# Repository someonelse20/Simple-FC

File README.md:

# Simple-FC

A RP2350 based flight controller with a 10-axis IMU. This board is designed to be used for drones and had four PWM outputs to control ESCs as well as UART and I2C to communicate with other boards.

## Overview
- **MCU**: RP2350
- **Gyroscope/Accelerometer**: LSM6DSM
- **Magnetometer**: MMC5983MA
- **Barometer**: BMP384
- **External Storage**: Micro SD card
- **MCU Storage**: 16MB
- **Input Voltage**: 1.2V-5.3V
- **I/O**: 
    - 4 PWM
    - 2 UART
    - 2 I2C
    - USB C

### Schematic

### PCB

## BOM
The BOM is located in BOM.csv and DigiKeyBOM.csv for ordering the parts from DikiKey. Alternatively the DigiKey BOM can be found [here](https://www.digikey.com/en/mylists/list/84RC15SOU8).

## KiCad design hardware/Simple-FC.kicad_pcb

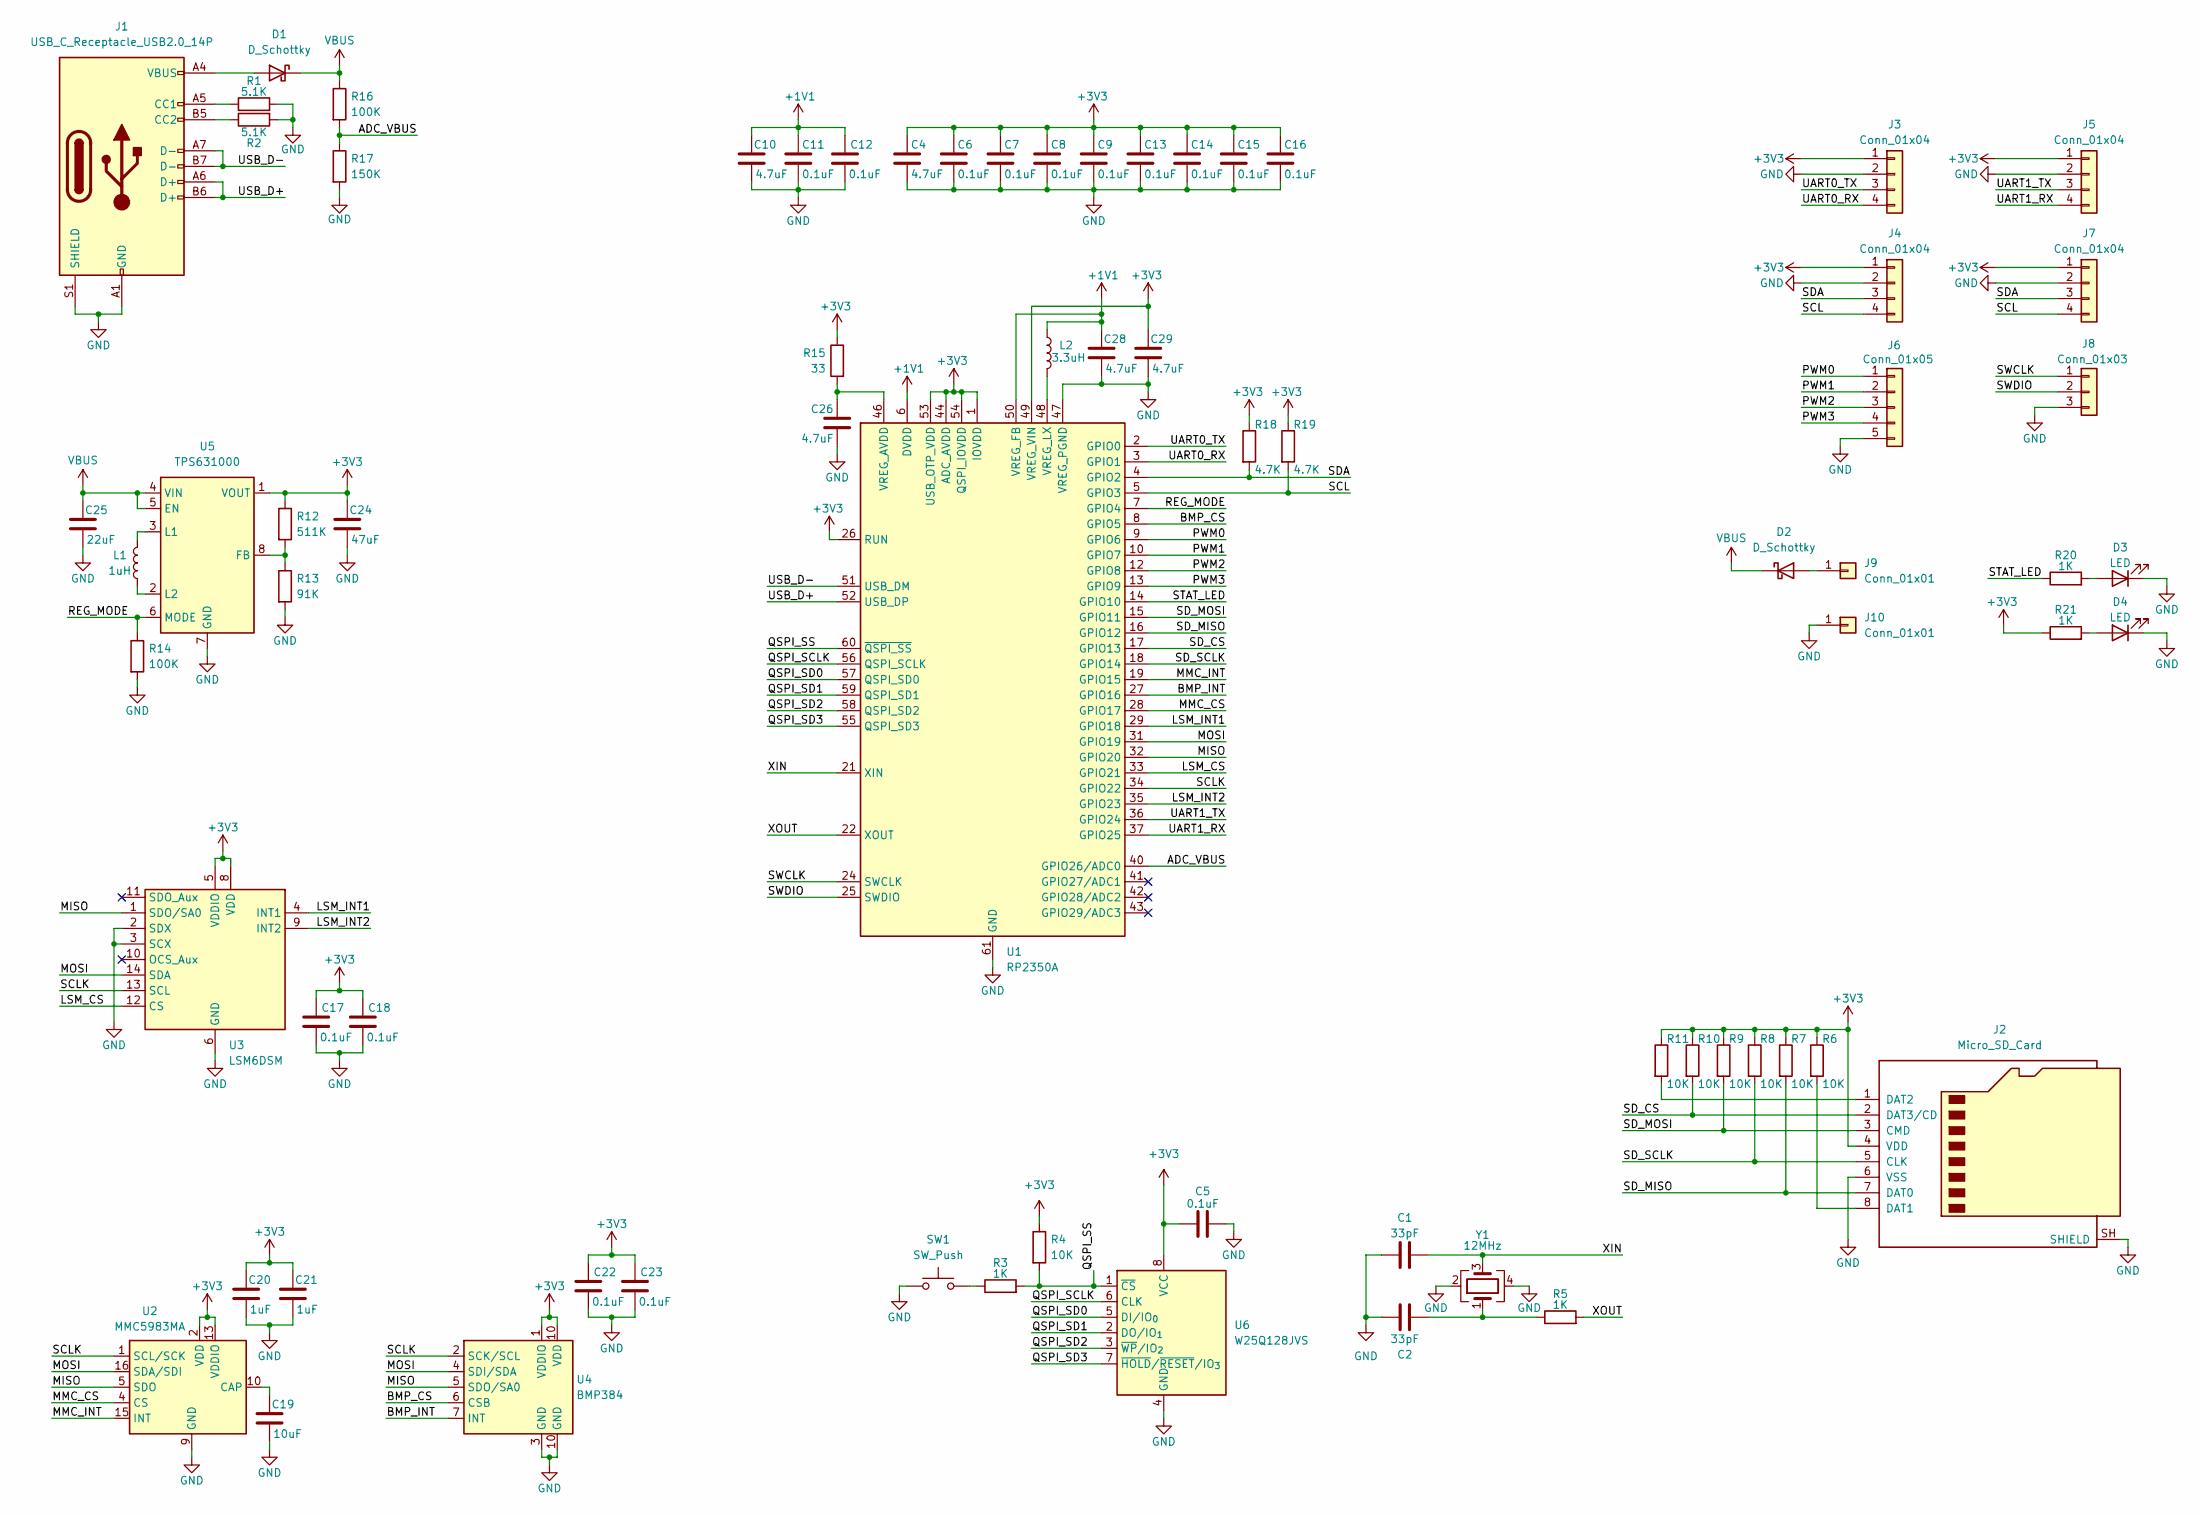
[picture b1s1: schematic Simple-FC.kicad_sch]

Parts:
C1, C2: 33pF; C_0402_1005Metric; MPN CL05C330JB5NNNC
C4, C10, C26, C28, C29: 4.7uF; C_0402_1005Metric; MPN GRM155R60J475ME47D
C5, C6, C7, C8, C9, C11, C12, C13, C14, C15, C16, C17, C18, C22, C23: 0.1uF; C_0402_1005Metric; MPN GRM155R71H104KE14D
C19: 10uF; C_0603_1608Metric; MPN GRM188R61A106ME69D
C20, C21: 1uF; C_0402_1005Metric; MPN CL05A105KO5NNNC
C24: 47uF; C_0603_1608Metric; MPN GRM188R60J476ME15D
C25: 22uF; C_0603_1608Metric; MPN C1608X5R0J226M080AC
D1, D2: D_Schottky; D_SMA; MPN SS210A
D3: LED; LED_0603_1608Metric; MPN LTST-C190GKT
D4: LED; LED_0603_1608Metric; MPN LTST-C190KRKT
J1: USB_C_Receptacle_USB2.0_14P; USB_C_Receptacle_HRO_TYPE-C-31-M-12; MPN UJ20-C-H-G-SMT-1-P16-TR
J2: Micro_SD_Card; microSD_HC_Molex_47219-2001; MPN MSD-7-A
J3, J4, J5, J7: Conn_01x04; PinHeader_1x04_P2.54mm_Vertical
J6: Conn_01x05; PinHeader_1x05_P2.54mm_Vertical
J8: Conn_01x03; PinHeader_1x03_P2.54mm_Vertical
J9, J10: Conn_01x01; SolderWirePad_1x01_SMD_1x2mm
L1: 1uH; L_0805_2012Metric; MPN DFE201210U-1R0M=P2
L2: 3.3uH; L_0805_2012Metric; MPN AOTA-B201610S3R3-101-T
R1, R2: 5.1K; R_0402_1005Metric; MPN RC0402FR-075K1L
R3, R5, R20, R21: 1K; R_0402_1005Metric; MPN ERJ-2RKF1001X
R4, R6, R7, R8, R9, R10, R11: 10K; R_0402_1005Metric; MPN RC0402FR-0710KL
R12: 511K; R_0402_1005Metric; MPN RC0402FR-13511KL
R13: 91K; R_0402_1005Metric; MPN RK73H1ETTP9102F
R14, R16: 100K; R_0402_1005Metric; MPN RC0402FR-07100KL
R15: 33; R_0402_1005Metric; MPN RC0402FR-0733RL
R17: 150K; R_0402_1005Metric; MPN CPF0402B150KE1
R18, R19: 4.7K; R_0402_1005Metric; MPN RK73H1ETTP4701F
SW1: SW_Push; SW_Push_SPST_NO_Alps_SKRK; MPN SKRKAEE020
U1: RP2350A; QFN-60-1EP_7x7mm_P0.4mm_EP3.4x3.4mm; MPN RP2350A
U2: MMC5983MA; LGA-16_3x3mm_P0.5mm; MPN MMC5983MA
U3: LSM6DSM; LGA-14_3x2.5mm_P0.5mm_LayoutBorder3x4y; MPN LSM6DSMTR
U4: BMP384; ST_HLGA-10_2x2mm_P0.5mm_LayoutBorder3x2y; MPN BMP384
U5: TPS631000; SOT-583-8; MPN TPS631000DRLR
U6: W25Q128JVS; Winbond_USON-8-1EP_3x2mm_P0.5mm_EP0.2x1.6mm; MPN W25Q128JVSIQ TR
Y1: 12MHz; Crystal_SMD_3225-4Pin_3.2x2.5mm; MPN ABM8-272-T3

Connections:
+1V1: C10.1, C11.1, C12.1, C28.1, L2.1, U1.6 (DVDD), U1.23 (DVDD), U1.39 (DVDD), U1.50 (VREG_FB)
/ADC_VBUS: R16.2, R17.1, U1.40 (GPIO26/ADC0)
/BMP_CS: U1.8 (GPIO5), U4.6 (CSB)
/BMP_INT: U1.27 (GPIO16), U4.7 (INT)
/LSM_CS: U1.33 (GPIO21), U3.12 (CS)
/LSM_INT1: U1.29 (GPIO18), U3.4 (INT1)
/LSM_INT2: U1.35 (GPIO23), U3.9 (INT2)
/MISO: U1.32 (GPIO20), U2.5 (SDO), U3.1 (SDO/SA0), U4.5 (SDO/SA0)
/MMC_CS: U1.28 (GPIO17), U2.4 (CS)
/MMC_INT: U1.19 (GPIO15), U2.15 (INT)
/MOSI: U1.31 (GPIO19), U2.16 (SDA/SDI), U3.14 (SDA), U4.4 (SDI/SDA)
/PWM0: J6.1, U1.9 (GPIO6)
/PWM1: J6.2, U1.10 (GPIO7)
/PWM2: J6.3, U1.12 (GPIO8)
/PWM3: J6.4, U1.13 (GPIO9)
/QSPI_SCLK: U1.56 (QSPI_SCLK), U6.6 (CLK)
/QSPI_SD0: U1.57 (QSPI_SD0), U6.5 (DI/IO_{0})
/QSPI_SD1: U1.59 (QSPI_SD1), U6.2 (DO/IO_{1})
/QSPI_SD2: U1.58 (QSPI_SD2), U6.3 (~WP/IO_{2})
/QSPI_SD3: U1.55 (QSPI_SD3), U6.7 (~HOLD/~RESET/IO_{3})
/QSPI_SS: R3.2, R4.2, U1.60 (~QSPI_SS), U6.1 (~CS)
/REG_MODE: R14.1, U1.7 (GPIO4), U5.6 (MODE)
/SCL: J4.4, J7.4, R19.2, U1.5 (GPIO3)
/SCLK: U1.34 (GPIO22), U2.1 (SCL/SCK), U3.13 (SCL), U4.2 (SCK/SCL)
/SDA: J4.3, J7.3, R18.2, U1.4 (GPIO2)
/SD_CS: J2.2 (DAT3/CD), R10.2, U1.17 (GPIO13)
/SD_MISO: J2.7 (DAT0), R7.2, U1.16 (GPIO12)
/SD_MOSI: J2.3 (CMD), R9.2, U1.15 (GPIO11)
/SD_SCLK: J2.5 (CLK), R8.2, U1.18 (GPIO14)
/STAT_LED: R20.1, U1.14 (GPIO10)
/SWCLK: J8.1, U1.24 (SWCLK)
/SWDIO: J8.2, U1.25 (SWDIO)
/UART0_RX: J3.4, U1.3 (GPIO1)
/UART0_TX: J3.3, U1.2 (GPIO0)
/UART1_RX: J5.4, U1.37 (GPIO25)
/UART1_TX: J5.3, U1.36 (GPIO24)
/USB_D+: J1.A6 (D+), J1.B6 (D+), U1.52 (USB_DP)
/USB_D-: J1.A7 (D-), J1.B7 (D-), U1.51 (USB_DM)
/XIN: C1.2, U1.21 (XIN), Y1.3
/XOUT: R5.2, U1.22 (XOUT)
unnamed: C2.1, R5.1, Y1.1
unnamed: D1.2 (A), J1.A4 (VBUS), J1.A9 (VBUS), J1.B4 (VBUS), J1.B9 (VBUS)
unnamed: D2.2 (A), J9.1 (Pin_1_1)
unnamed: D3.2 (A), R20.2
unnamed: D4.2 (A), R21.2
unnamed: J1.A5 (CC1), R1.1
unnamed: J1.B5 (CC2), R2.1
unnamed: J2.8 (DAT1), R6.2
unnamed: J2.1 (DAT2), R11.2
unnamed: R3.1, SW1.2
unnamed: C26.1, R15.2, U1.46 (VREG_AVDD)
unnamed: L2.2, U1.48 (VREG_LX)
unnamed: C19.1, U2.10 (CAP)
unnamed: R12.2, R13.1, U5.8 (FB)
unnamed: L1.1, U5.3 (L1)
unnamed: L1.2, U5.2 (L2)
VBUS: C25.1, D1.1 (K), D2.1 (K), R16.1, U5.4 (VIN), U5.5 (EN)

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
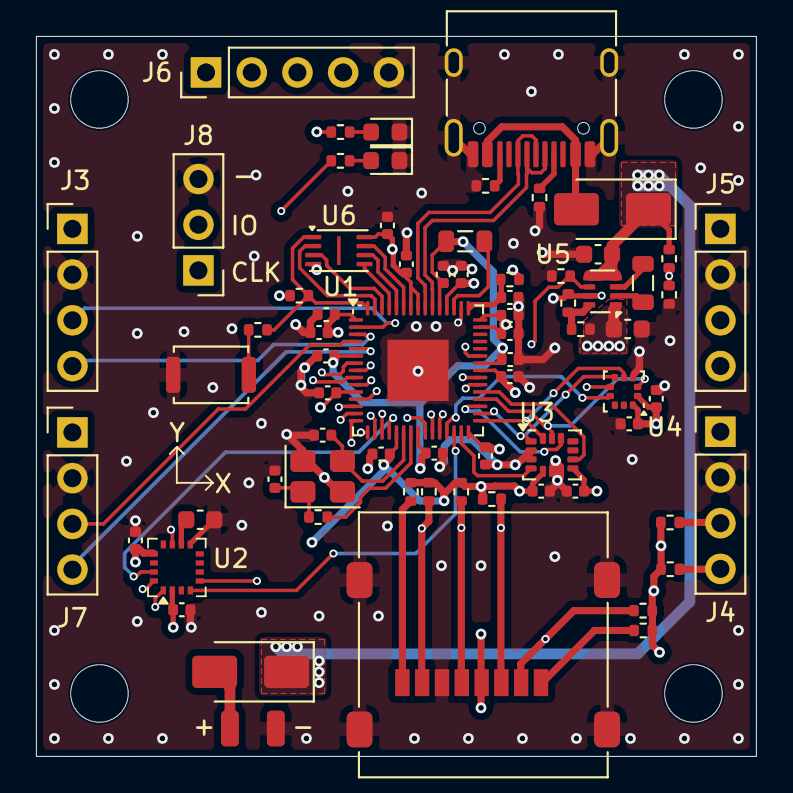
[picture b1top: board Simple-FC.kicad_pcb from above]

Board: 4 copper layers, 40.0 x 40.0 mm, 72 parts (0 on the bottom side), 59 nets.

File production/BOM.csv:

"Reference","Qty","Value","DNP","Exclude from BOM","Exclude from Board","Exclude from Simulation","Exclude from Position Files","Footprint","Datasheet","MPN"
"SW1","1","SW_Push","","","","","${EXCLUDE_FROM_POS_FILES}","Button_Switch_SMD:SW_Push_SPST_NO_Alps_SKRK","","SKRKAEE020"
"C1,C2","2","33pF","","","","","${EXCLUDE_FROM_POS_FILES}","Capacitor_SMD:C_0402_1005Metric","","CL05C330JB5NNNC"
"C4,C10,C26,C28,C29","5","4.7uF","","","","","${EXCLUDE_FROM_POS_FILES}","Capacitor_SMD:C_0402_1005Metric","","GRM155R60J475ME47D"
"C5,C6,C7,C8,C9,C11,C12,C13,C14,C15,C16,C17,C18,C22,C23","15","0.1uF","","","","","${EXCLUDE_FROM_POS_FILES}","Capacitor_SMD:C_0402_1005Metric","","GRM155R71H104KE14D"
"C20,C21","2","1uF","","","","","${EXCLUDE_FROM_POS_FILES}","Capacitor_SMD:C_0402_1005Metric","","CL05A105KO5NNNC"
"C19","1","10uF","","","","","${EXCLUDE_FROM_POS_FILES}","Capacitor_SMD:C_0603_1608Metric","","GRM188R61A106ME69D"
"C24","1","47uF","","","","","${EXCLUDE_FROM_POS_FILES}","Capacitor_SMD:C_0603_1608Metric","","GRM188R60J476ME15D"
"C25","1","22uF","","","","","${EXCLUDE_FROM_POS_FILES}","Capacitor_SMD:C_0603_1608Metric","","C1608X5R0J226M080AC"
"J2","1","Micro_SD_Card","","","","","${EXCLUDE_FROM_POS_FILES}","Connector_Card:microSD_HC_Molex_47219-2001","https://www.we-online.com/components/products/datasheet/6930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","MSD-7-A"
"J8","1","Conn_01x03","DNP","","","","${EXCLUDE_FROM_POS_FILES}","Connector_PinHeader_2.54mm:PinHeader_1x03_P2.54mm_Vertical","",""
"J3,J4,J5,J7","4","Conn_01x04","DNP","","","","${EXCLUDE_FROM_POS_FILES}","Connector_PinHeader_2.54mm:PinHeader_1x04_P2.54mm_Vertical","",""
"J6","1","Conn_01x05","DNP","","","","${EXCLUDE_FROM_POS_FILES}","Connector_PinHeader_2.54mm:PinHeader_1x05_P2.54mm_Vertical","",""
"J1","1","USB_C_Receptacle_USB2.0_14P","","","","","${EXCLUDE_FROM_POS_FILES}","Connector_USB:USB_C_Receptacle_HRO_TYPE-C-31-M-12","https://www.usb.org/sites/default/files/documents/usb_type-c.zip","UJ20-C-H-G-SMT-1-P16-TR"
"J9,J10","2","Conn_01x01","DNP","","","","${EXCLUDE_FROM_POS_FILES}","Connector_Wire:SolderWirePad_1x01_SMD_1x2mm","",""
"Y1","1","12MHz","","","","","${EXCLUDE_FROM_POS_FILES}","Crystal:Crystal_SMD_3225-4Pin_3.2x2.5mm","","ABM8-272-T3"
"D1,D2","2","D_Schottky","","","","","${EXCLUDE_FROM_POS_FILES}","Diode_SMD:D_SMA","","SS210A"
"L1","1","1uH","","","","","${EXCLUDE_FROM_POS_FILES}","Inductor_SMD:L_0805_2012Metric","","DFE201210U-1R0M=P2"
"L2","1","3.3uH","","","","","${EXCLUDE_FROM_POS_FILES}","Inductor_SMD:L_0805_2012Metric","","AOTA-B201610S3R3-101-T"
"D3,D4","2","LED","","","","","${EXCLUDE_FROM_POS_FILES}","LED_SMD:LED_0603_1608Metric","","LTST-C190GKT,LTST-C190KRKT"
"U1","1","RP2350A","","","","","${EXCLUDE_FROM_POS_FILES}","Package_DFN_QFN:QFN-60-1EP_7x7mm_P0.4mm_EP3.4x3.4mm","https://datasheets.raspberrypi.com/rp2350/rp2350-datasheet.pdf","RP2350A"
"U3","1","LSM6DSM","","","","","${EXCLUDE_FROM_POS_FILES}","Package_LGA:LGA-14_3x2.5mm_P0.5mm_LayoutBorder3x4y","https://www.st.com/resource/en/datasheet/lsm6dsm.pdf","LSM6DSMTR"
"U2","1","MMC5983MA","","","","","${EXCLUDE_FROM_POS_FILES}","Package_LGA:LGA-16_3x3mm_P0.5mm","https://www.memsic.com/Public/Uploads/uploadfile/files/20220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","MMC5983MA"
"U4","1","BMP384","","","","","${EXCLUDE_FROM_POS_FILES}","Package_LGA:ST_HLGA-10_2x2mm_P0.5mm_LayoutBorder3x2y","https://www.bosch-sensortec.com/media/boschsensortec/downloa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","BMP384"
"U6","1","W25Q128JVS","","","","","${EXCLUDE_FROM_POS_FILES}","Package_SON:Winbond_USON-8-1EP_3x2mm_P0.5mm_EP0.2x1.6mm","https://www.winbond.com/resource-files/w25q128jv_dtr%20revc%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","W25Q128JVSIQ TR"
"U5","1","TPS631000","","","","","${EXCLUDE_FROM_POS_FILES}","Package_TO_SOT_SMD:SOT-583-8","https://www.ti.com/lit/ds/symlink/tps631000.pdf","TPS631000DRLR"
"R1,R2","2","5.1K","","","","","${EXCLUDE_FROM_POS_FILES}","Resistor_SMD:R_0402_1005Metric","","RC0402FR-075K1L"
"R3,R5,R20,R21","4","1K","","","","","${EXCLUDE_FROM_POS_FILES}","Resistor_SMD:R_0402_1005Metric","","ERJ-2RKF1001X"
"R4,R6,R7,R8,R9,R10,R11","7","10K","","","","","${EXCLUDE_FROM_POS_FILES}","Resistor_SMD:R_0402_1005Metric","","RC0402FR-0710KL"
"R12","1","511K","","","","","${EXCLUDE_FROM_POS_FILES}","Resistor_SMD:R_0402_1005Metric","","RC0402FR-13511KL"
"R13","1","91K","","","","","${EXCLUDE_FROM_POS_FILES}","Resistor_SMD:R_0402_1005Metric","","RK73H1ETTP9102F"
"R14,R16","2","100K","","","","","${EXCLUDE_FROM_POS_FILES}","Resistor_SMD:R_0402_1005Metric","","RC0402FR-07100KL"
"R15","1","33","","","","","${EXCLUDE_FROM_POS_FILES}","Resistor_SMD:R_0402_1005Metric","","RC0402FR-0733RL"
"R17","1","150K","","","","","${EXCLUDE_FROM_POS_FILES}","Resistor_SMD:R_0402_1005Metric","","CPF0402B150KE1"
"R18,R19","2","4.7K","","","","","${EXCLUDE_FROM_POS_FILES}","Resistor_SMD:R_0402_1005Metric","","RK73H1ETTP4701F"

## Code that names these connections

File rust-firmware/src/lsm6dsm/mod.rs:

//! # SPI DMA Example
//!
//! This application demonstrates how to use DMA for SPI transfers.
//!
//! The application expects the MISO and MOSI pins to be wired together so that it is able to check
//! whether the data was sent and received correctly.
//!
//! See the `Cargo.toml` file for Copyright and licence details.

use embedded_hal::spi::SpiDevice;
use embedded_hal_bus::spi::ExclusiveDevice;
// Ensure we halt the program on panic (if we don't mention this crate it won't
// be linked)
use panic_halt as _;

// Alias for our HAL crate
use rp235x_hal as hal;

// Some things we need
use hal::clocks::Clock;
use hal::fugit::RateExtU32;

/// External high-speed crystal on the Raspberry Pi Pico 2 board is 12 MHz.
/// Adjust if your board has a different frequency
const XTAL_FREQ_HZ: u32 = 12_000_000u32;

mod regs;

pub struct Lsm6dsm {
    // spi: ExclusiveDevice<hal::spi::Spi<_, _, _, 8>, hal::gpio::Pins, hal::Timer<_>>,

    pub gyro: [f32; 3],
    pub accel: [f32; 3],
    pub temp: i16,
}

impl Lsm6dsm {
    pub fn new() {
        // Grab our singleton objects
        let mut pac = hal::pac::Peripherals::take().unwrap();

        // Set up the watchdog driver - needed by the clock setup code
        let mut watchdog = hal::Watchdog::new(pac.WATCHDOG);

        // Configure the clocks
        let clocks = hal::clocks::init_clocks_and_plls(
            XTAL_FREQ_HZ,
            pac.XOSC,
            pac.CLOCKS,
            pac.PLL_SYS,
            pac.PLL_USB,
            &mut pac.RESETS,
            &mut watchdog,
        )
        .unwrap();

        let mut timer = hal::Timer::new_timer0(pac.TIMER0, &mut pac.RESETS, &clocks);

        // The single-cycle I/O block controls our GPIO pins
        let sio = hal::Sio::new(pac.SIO);

        // Set the pins to their default state
        let pins = hal::gpio::Pins::new(
            pac.IO_BANK0,
            pac.PADS_BANK0,
            sio.gpio_bank0,
            &mut pac.RESETS,
        );

        // These are implicitly used by the spi driver if they are in the correct mode
        let spi_mosi = pins.gpio7.into_function::<hal::gpio::FunctionSpi>();
        let spi_miso = pins.gpio4.into_function::<hal::gpio::FunctionSpi>();
        let spi_sclk = pins.gpio6.into_function::<hal::gpio::FunctionSpi>();
        let spi_bus = hal::spi::Spi::<_, _, _, 8>::new(pac.SPI0, (spi_mosi, spi_miso, spi_sclk));

        // Exchange the uninitialised SPI driver for an initialised one
        let spi_bus = spi_bus.init(
            &mut pac.RESETS,
            clocks.peripheral_clock.freq(),
            16.MHz(),
            embedded_hal::spi::MODE_0,
        );

        let spi_cs = pins.gpio8.into_function::<hal::gpio::FunctionSioOutput>();
        let mut spi = ExclusiveDevice::new(spi_bus, spi_cs, &mut timer).unwrap();
    }

    pub fn set_conf() {

    }

    pub fn check() -> bool {
        return true;
    }

    pub fn poll() -> [i32; 6] {
        let data_out: [i32; 6] = [0, 0, 0, 0, 0, 0];
        return data_out;
    }
}


// End of file
